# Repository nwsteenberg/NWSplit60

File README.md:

# NWSplit60 Keyboard
NWSplit80 is a split, column staggered, ergonomic keyboard designed for ISO layout. 

------------------------------------------------

------------------------------------------------

## Features: 
* Column Staggered
* Asymetric to support ISO layout
* Thumb cluster and inner stretch keys on both sides
* RP2040-zero controller
* Hotswap MX switches

## Firmware:
- QMK: `#INSERT LINK`
- VIAL:  `#INSERT LINK`

## TODO:
- [ ] Images
- [ ] QMK PR
- [ ] VIAL PR
- [ ] File Structure
- [ ] Build Guide
- [ ] Detailed BOM

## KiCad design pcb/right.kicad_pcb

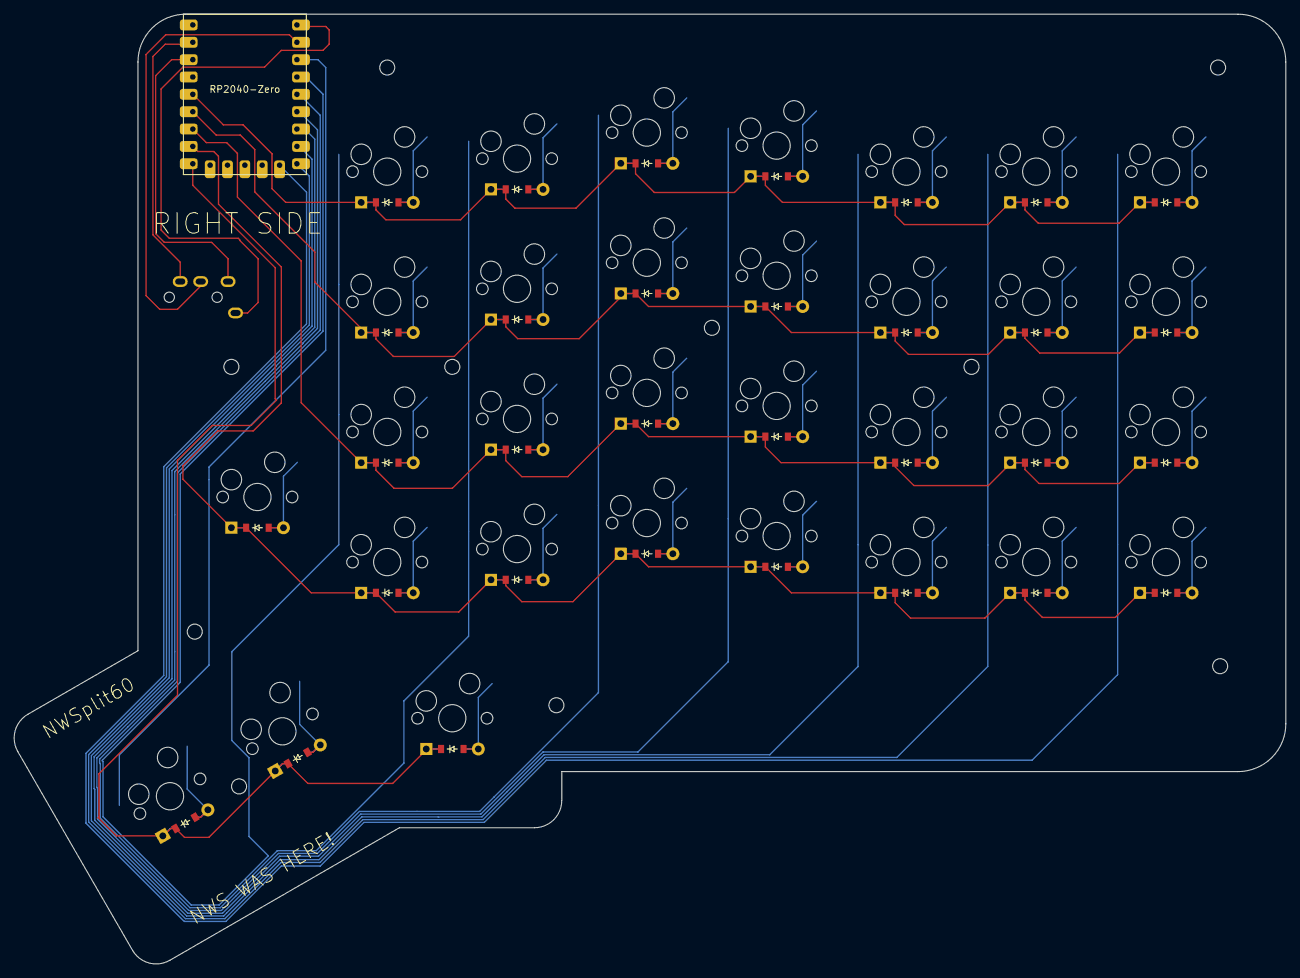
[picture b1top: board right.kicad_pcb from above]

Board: 2 copper layers, 186.1 x 139.0 mm, 75 parts (0 on the bottom side), 45 nets.

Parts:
D1, D2, D3, D4, D5, D6, D7, D8, D9, D10, D11, D12, D13, D14, D15, D16, D17, D18, D19, D20, D21, D22, D23, D24, D25, D26, D27, D28, D29, D30, D31, D32: ComboDiode
MH1, MH2, MH3, MH4, MH5, MH6, MH7, MH8, MH9, MH10: mounting_hole_npth
S1, S2, S3, S4, S5, S6, S7, S8, S9, S10, S11, S12, S13, S14, S15, S16, S17, S18, S19, S20, S21, S22, S23, S24, S25, S26, S27, S28, S29, S30, S31, S32: MX
TRRS1: trrs_pj320a

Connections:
GP2: S29.1, S32.1
GP3: S25.1, S26.1, S27.1, S28.1, S31.1
GP4: S21.1, S22.1, S23.1, S24.1, S30.1
GP5: S17.1, S18.1, S19.1, S20.1
GP6: S13.1, S14.1, S15.1, S16.1
GP7: S9.1, S10.1, S11.1, S12.1
GP8: S5.1, S6.1, S7.1, S8.1
GP9: S1.1, S2.1, S3.1, S4.1
GP14: D30.1, D31.1, D32.1
GP15: D1.1, D5.1, D9.1, D13.1, D17.1, D21.1, D25.1, D29.1
GP26: D2.1, D6.1, D10.1, D14.1, D18.1, D22.1, D26.1
GP27: D3.1, D7.1, D11.1, D15.1, D19.1, D23.1, D27.1
GP28: D4.1, D8.1, D12.1, D16.1, D20.1, D24.1, D28.1
mirror_center_only: D31.2, S31.2
mirror_index_bottom: D21.2, S21.2
mirror_index_home: D22.2, S22.2
mirror_index_num: D24.2, S24.2
mirror_index_top: D23.2, S23.2
mirror_inner_bottom: D25.2, S25.2
mirror_inner_home: D26.2, S26.2
mirror_inner_num: D28.2, S28.2
mirror_inner_top: D27.2, S27.2
mirror_middle_bottom: D17.2, S17.2
mirror_middle_home: D18.2, S18.2
mirror_middle_num: D20.2, S20.2
mirror_middle_top: D19.2, S19.2
mirror_outer_bottom: D5.2, S5.2
mirror_outer_home: D6.2, S6.2
mirror_outer_num: D8.2, S8.2
mirror_outer_top: D7.2, S7.2
mirror_pinky_bottom: D9.2, S9.2
mirror_pinky_home: D10.2, S10.2
mirror_pinky_num: D12.2, S12.2
mirror_pinky_top: D11.2, S11.2
mirror_reach_only: D32.2, S32.2
mirror_reachy_bottom: D1.2, S1.2
mirror_reachy_home: D2.2, S2.2
mirror_reachy_num: D4.2, S4.2
mirror_reachy_top: D3.2, S3.2
mirror_ring_bottom: D13.2, S13.2
mirror_ring_home: D14.2, S14.2
mirror_ring_num: D16.2, S16.2
mirror_ring_top: D15.2, S15.2
mirror_stretch_bottom: D29.2, S29.2
mirror_tuck_only: D30.2, S30.2

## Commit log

2025-10-10 Added ergogen footprint
2025-10-12 Added Vial/QMK firmware
2025-10-22 Updated ergogen with new bottom plate. Fixed up errors in keymap
2025-10-25 Fixed up tolerances
